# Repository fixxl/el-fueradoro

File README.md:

# el-fueradoro

This project contains a remotely controlled ignition system for audio-fireworks based on ATmega328P and RFM69CW.
Further information (in German) is given in [the user manual](https://cdn.jsdelivr.net/gh/fixxl/el-fueradoro@master/Manual/fueradoro.pdf).

What the system is capable of doing can be seen in our [new year's fireworks 2015](https://vimeo.com/116115628), [new year's fireworks 2016](https://vimeo.com/150594996), [new year's fireworks 2017](https://www.youtube.com/watch?v=Rc5oZRx3s50), [new year's fireworks 2018](https://www.youtube.com/watch?v=unH9tJSg1mw), and [new year's fireworks 2019](https://www.youtube.com/watch?v=GiKSdqZKpVQ).

Copyright:

All parts of the project are licensed under: https://creativecommons.org/licenses/by-nc/3.0/de/

Usage to perform commercial firework shows is explicitly granted.
Selling hard- and software derived from this project and usage within commercial systems is prohibited.

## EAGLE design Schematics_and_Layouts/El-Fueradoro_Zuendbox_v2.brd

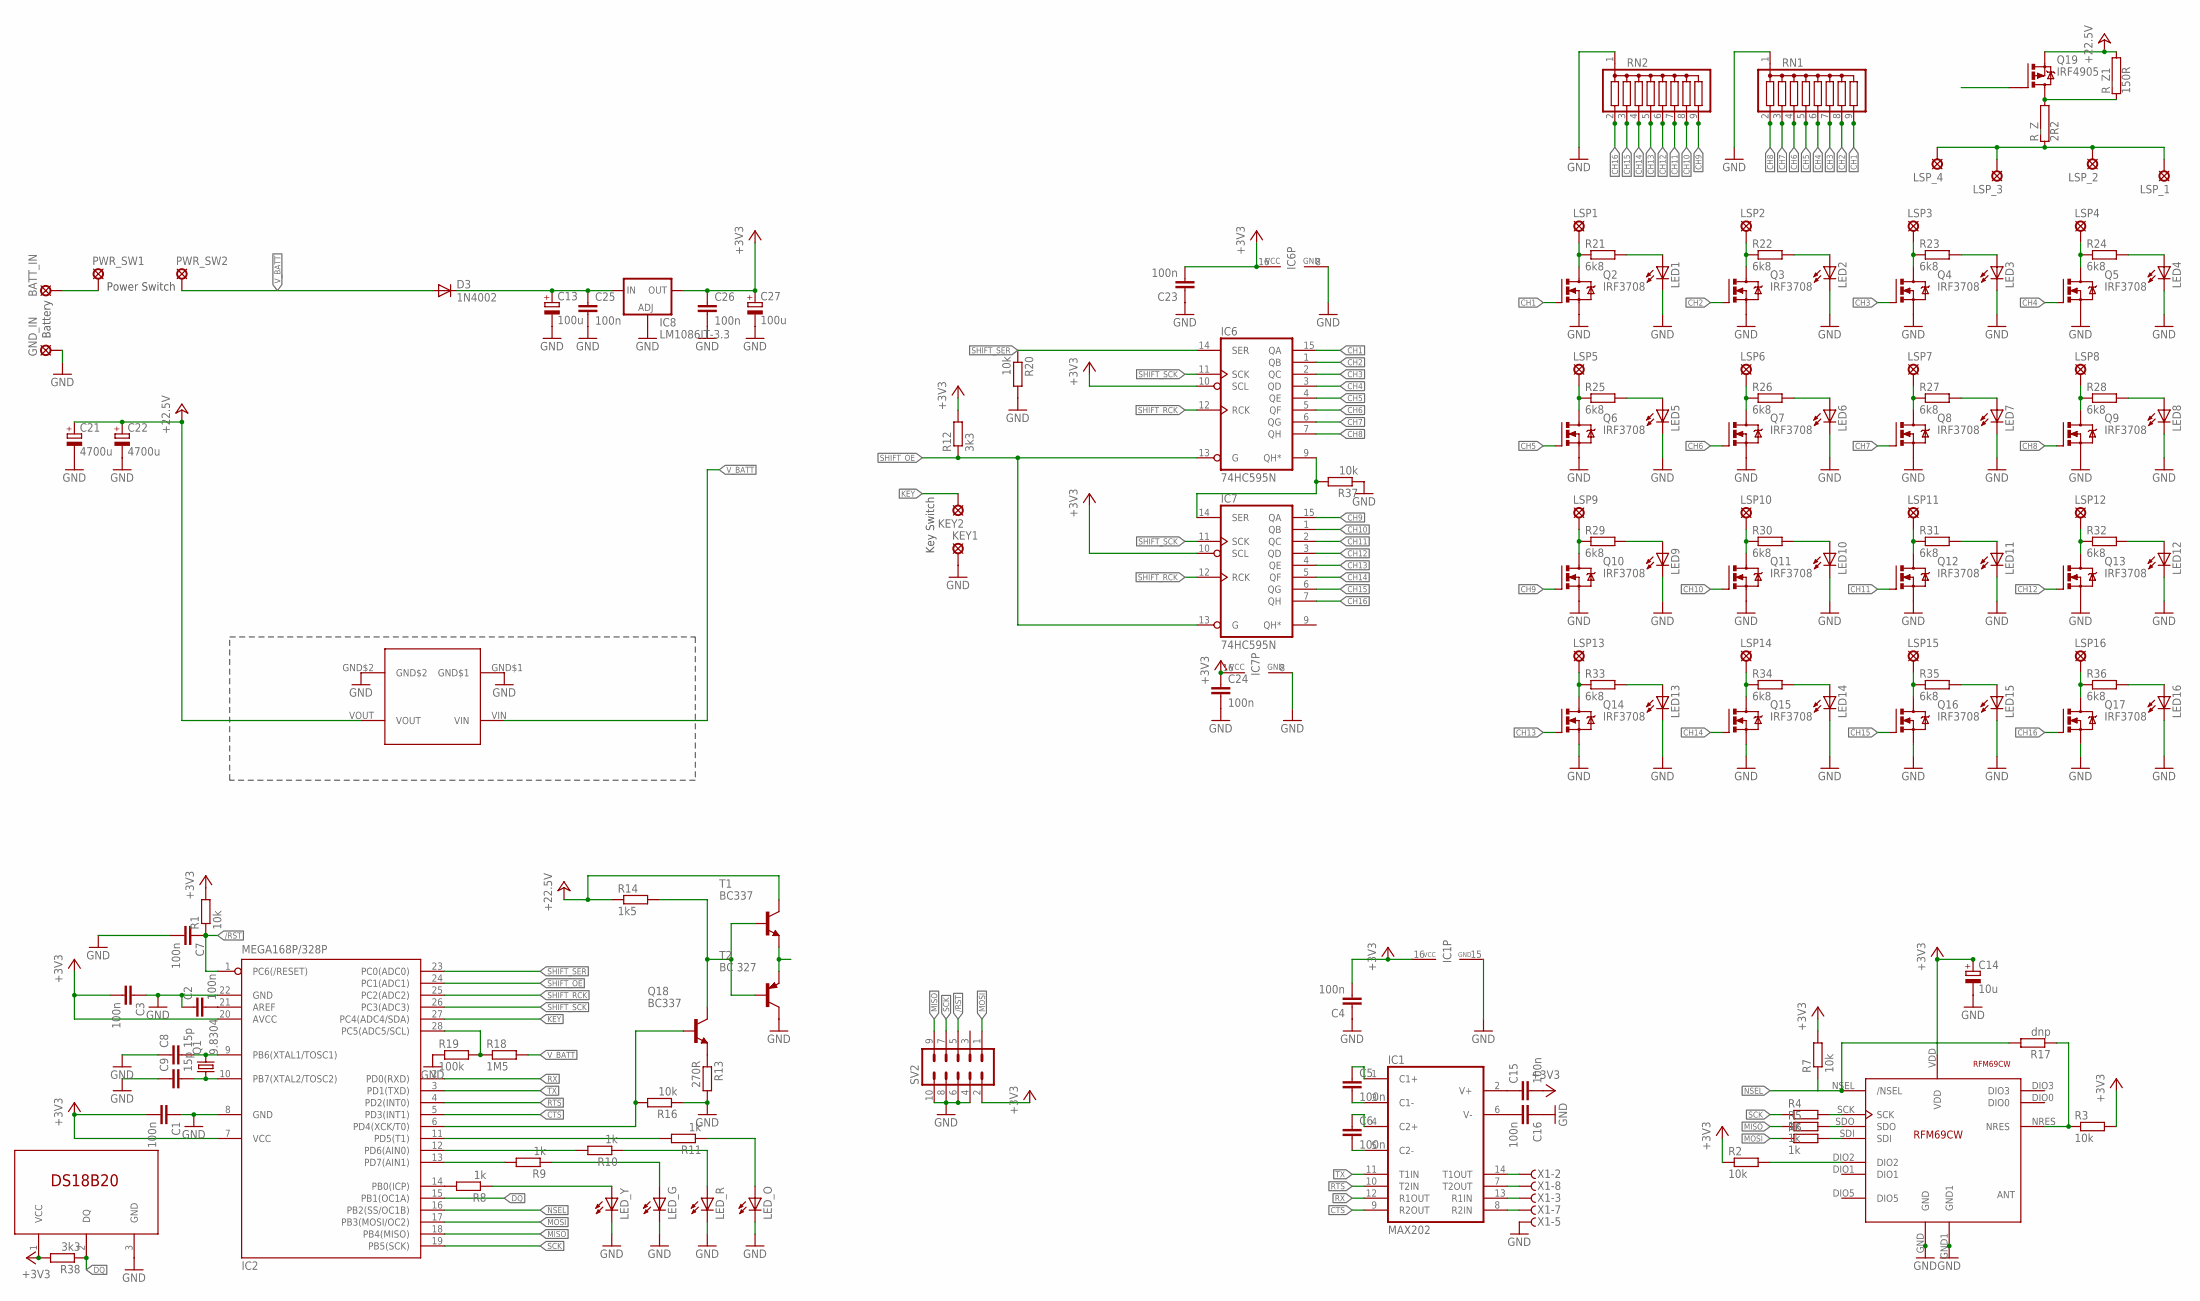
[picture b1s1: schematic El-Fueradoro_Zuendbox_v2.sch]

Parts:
BATT_IN: LSP10
C1, C2, C3, C4, C5, C6, C7, C15, C16, C23, C24, C25, C26: 100n; C025-024X044
C8, C9: 15p; C025-024X044
C13, C27: 100u; B45181A
C14: 10u; B45181A
C21, C22: 4700u; E7,5-18
D3: 1N4002; DO41-10
GND_IN: LSP10
IC1: MAX202; DIL16
IC2: MEGA168P/328P; DIL28-3
IC6, IC7: 74HC595N; DIL16
IC8: LM1086IT-3.3; TO220L1
KEY1, KEY2: LSP10
LED1, LED2, LED3, LED4, LED5, LED6, LED7, LED8, LED9, LED10, LED11, LED12, LED13, LED14, LED15, LED16: LED3MM
LED_G: LED5MM
LED_O: LED5MM
LED_R: LED5MM
LED_Y: LED5MM
LSP1: CH1; LSP11
LSP2: CH2; LSP11
LSP3: CH3; LSP11
LSP4: CH4; LSP11
LSP5: CH5; LSP11
LSP6: CH6; LSP11
LSP7: CH7; LSP11
LSP8: CH8; LSP11
LSP9: CH9; LSP11
LSP10: CH10; LSP11
LSP11: CH11; LSP11
LSP12: CH12; LSP11
LSP13: CH13; LSP11
LSP14: CH14; LSP11
LSP15: CH15; LSP11
LSP16: CH16; LSP11
LSP_1, LSP_2, LSP_3, LSP_4: LSP11
PWR_SW1, PWR_SW2: LSP10
Q1: 9.8304; HC49/S
Q2, Q3, Q4, Q5, Q6, Q7, Q8, Q9, Q10, Q11, Q12, Q13, Q14, Q15, Q16, Q17: IRF3708; TO220BV
Q18: BC337; TO92
Q19: IRF4905; TO220BV
R1, R2, R3, R7, R16, R20, R37: 10k; 0207/10
R4, R5, R6, R8, R9, R10, R11: 1k; 0207/10
R12, R38: 3k3; 0207/10
R13: 270R; 0207/10
R14: 1k5; 0207/10
R17: dnp; 0207/10
R18: 1M5; 0207/10
R19: 100k; 0207/10
R21, R22, R23, R24, R25, R26, R27, R28, R29, R30, R31, R32, R33, R34, R35, R36: 6k8; 0207/10
RN1, RN2: G08R; SIL9
R_Z: 2R2; KH214R-8
R_Z1: 150R; KH214R-8
SV2: ML10
T1: BC337; TO92
T2: BC 327; TO92
U$2: DS18B20; TO92-LINE
U$3: XL6009_MODULED; XL6009_PACK
U$4: RFM69CW
X1: F09HPS; F09HP

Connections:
+3V3: C1.2, C3.2, C4.2, C14.+, C15.2, C23.2, C24.1, C26.1, C27.+, IC1.16 (VCC), IC2.7 (VCC), IC2.20 (AVCC), IC6.10 (SCL), IC6.16 (VCC), IC7.10 (SCL), IC7.16 (VCC), IC8.2 (OUT), R1.2, R2.1, R3.2, R7.2, R12.2, R38.2, SV2.2, U$2.1 (VCC), U$4.VDD
+22_5V: C21.+, C22.+, Q19.S, R14.1, R_Z1.2, T1.3 (C), U$3.VOUT
/RST: C7.1, IC2.1 (PC6(/RESET)), R1.1, SV2.5
CH1: IC6.15 (QA), Q2.G, RN1.9
CH2: IC6.1 (QB), Q3.G, RN1.8
CH3: IC6.2 (QC), Q4.G, RN1.7
CH4: IC6.3 (QD), Q5.G, RN1.6
CH5: IC6.4 (QE), Q6.G, RN1.5
CH6: IC6.5 (QF), Q7.G, RN1.4
CH7: IC6.6 (QG), Q8.G, RN1.3
CH8: IC6.7 (QH), Q9.G, RN1.2
CH9: IC7.15 (QA), Q10.G, RN2.9
CH10: IC7.1 (QB), Q11.G, RN2.8
CH11: IC7.2 (QC), Q12.G, RN2.7
CH12: IC7.3 (QD), Q13.G, RN2.6
CH13: IC7.4 (QE), Q14.G, RN2.5
CH14: IC7.5 (QF), Q15.G, RN2.4
CH15: IC7.6 (QG), Q16.G, RN2.3
CH16: IC7.7 (QH), Q17.G, RN2.2
CTS: IC1.9 (R2OUT), IC2.5 (PD3(INT1))
DQ: IC2.15 (PB1(OC1A)), R38.1, U$2.2 (DQ)
DRVBASE: Q18.3 (C), R14.2, T1.2 (B), T2.2 (B)
GND: C1.1, C2.1, C3.1, C4.1, C7.2, C8.1, C9.1, C13.-, C14.-, C16.1, C21.-, C22.-, C23.1, C24.2, C25.2, C26.2, C27.-, GND_IN.MP, IC1.15 (GND), IC2.8 (GND), IC2.22 (GND), IC6.8 (GND), IC7.8 (GND), IC8.1 (ADJ), KEY1.MP, LED1.K (C), LED2.K (C), LED3.K (C), LED4.K (C), LED5.K (C), LED6.K (C), LED7.K (C), LED8.K (C), LED9.K (C), LED10.K (C), LED11.K (C), LED12.K (C), LED13.K (C), LED14.K (C), LED15.K (C), LED16.K (C), LED_G.K (C), LED_O.K (C), LED_R.K (C), LED_Y.K (C), Q2.S, Q3.S, Q4.S, Q5.S, Q6.S, Q7.S, Q8.S, Q9.S, Q10.S, Q11.S, Q12.S, Q13.S, Q14.S, Q15.S, Q16.S, Q17.S, R13.2, R16.1, R19.1, R20.2, R37.1, RN1.1, RN2.1, SV2.4, SV2.6, SV2.8, SV2.10, T2.3 (C), U$2.3 (GND), U$3.GND$1, U$3.GND$2, U$4.GND, U$4.GND1, X1.5 (F)
KEY: IC2.27 (PC4(ADC4/SDA)), KEY2.MP
MISO: IC2.18 (PB4(MISO)), R5.1, SV2.9
MOSI: IC2.17 (PB3(MOSI/OC2)), R6.1, SV2.1
unnamed: BATT_IN.MP, PWR_SW1.MP
unnamed: C13.+, C25.1, D3.C, IC8.3 (IN)
unnamed: IC2.6 (PD4(XCK/T0)), Q18.2 (B), R16.2
unnamed: Q18.1 (E), R13.1
unnamed: LSP_1.MP, LSP_2.MP, LSP_3.MP, LSP_4.MP, R_Z.1
unnamed: Q19.D, R_Z.2, R_Z1.1
unnamed: R2.2, U$4.DIO2
unnamed: R4.2, U$4.SCK
unnamed: R5.2, U$4.SDO
unnamed: R6.2, U$4.SDI
unnamed: R3.1, R17.1, U$4.NRES
unnamed: C2.2, IC2.21 (AREF)
unnamed: C9.2, IC2.10 (PB7(XTAL2/TOSC2)), Q1.1
unnamed: C5.1, IC1.1 (C1+)
unnamed: C5.2, IC1.3 (C1-)
unnamed: C6.1, IC1.4 (C2+)
unnamed: C6.2, IC1.5 (C2-)
unnamed: C8.2, IC2.9 (PB6(XTAL1/TOSC1)), Q1.2
unnamed: IC2.13 (PD7(AIN1)), R9.2
unnamed: IC2.12 (PD6(AIN0)), R10.2
unnamed: IC2.11 (PD5(T1)), R11.2
unnamed: LED_O.A, R11.1
unnamed: IC2.14 (PB0(ICP)), R8.2
unnamed: LED_R.A, R10.1
unnamed: LED_G.A, R9.1
unnamed: LED_Y.A, R8.1
unnamed: IC2.28 (PC5(ADC5/SCL)), R18.1, R19.2
unnamed: C15.1, IC1.2 (V+)
unnamed: C16.2, IC1.6 (V-)
unnamed: IC6.9 (QH*), IC7.14 (SER), R37.2
unnamed: LSP1.MP, Q2.D, R21.1
unnamed: LSP2.MP, Q3.D, R22.1
unnamed: LSP3.MP, Q4.D, R23.1
unnamed: LSP4.MP, Q5.D, R24.1
unnamed: LSP5.MP, Q6.D, R25.1
unnamed: LSP6.MP, Q7.D, R26.1
unnamed: LSP7.MP, Q8.D, R27.1
unnamed: LSP8.MP, Q9.D, R28.1
unnamed: LSP9.MP, Q10.D, R29.1
unnamed: LSP10.MP, Q11.D, R30.1
unnamed: LSP11.MP, Q12.D, R31.1
unnamed: LSP12.MP, Q13.D, R32.1
unnamed: LSP13.MP, Q14.D, R33.1
unnamed: LSP14.MP, Q15.D, R34.1
unnamed: LSP15.MP, Q16.D, R35.1
unnamed: LSP16.MP, Q17.D, R36.1
unnamed: LED1.A, R21.2
unnamed: LED2.A, R22.2
unnamed: LED3.A, R23.2
unnamed: LED4.A, R24.2
unnamed: LED5.A, R25.2
unnamed: LED6.A, R26.2
unnamed: LED7.A, R27.2
unnamed: LED8.A, R28.2
unnamed: LED9.A, R29.2
unnamed: LED10.A, R30.2
unnamed: LED11.A, R31.2
unnamed: LED12.A, R32.2
unnamed: LED13.A, R33.2
unnamed: LED14.A, R34.2
unnamed: LED15.A, R35.2
unnamed: LED16.A, R36.2
NSEL: IC2.16 (PB2(SS/OC1B)), R7.1, R17.2, U$4.NSEL (/NSEL)
PC_CTS_IN: IC1.7 (T2OUT), X1.8 (F)
PC_RTS_OUT: IC1.8 (R2IN), X1.7 (F)
PC_RX_IN: IC1.14 (T1OUT), X1.2 (F)
PC_TX_OUT: IC1.13 (R1IN), X1.3 (F)
PMOSG: Q19.G, T1.1 (E), T2.1 (E)
RTS: IC1.10 (T2IN), IC2.4 (PD2(INT0))
RX: IC1.12 (R1OUT), IC2.2 (PD0(RXD))
SCK: IC2.19 (PB5(SCK)), R4.1, SV2.7
SHIFT_OE: IC2.24 (PC1(ADC1)), IC6.13 (G), IC7.13 (G), R12.1
SHIFT_RCK: IC2.25 (PC2(ADC2)), IC6.12 (RCK), IC7.12 (RCK)
SHIFT_SCK: IC2.26 (PC3(ADC3)), IC6.11 (SCK), IC7.11 (SCK)
SHIFT_SER: IC2.23 (PC0(ADC0)), IC6.14 (SER), R20.1
TX: IC1.11 (T1IN), IC2.3 (PD1(TXD))
V_BATT: D3.A, PWR_SW2.MP, R18.2, U$3.VIN

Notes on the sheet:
Power Switch
Battery
Key Switch

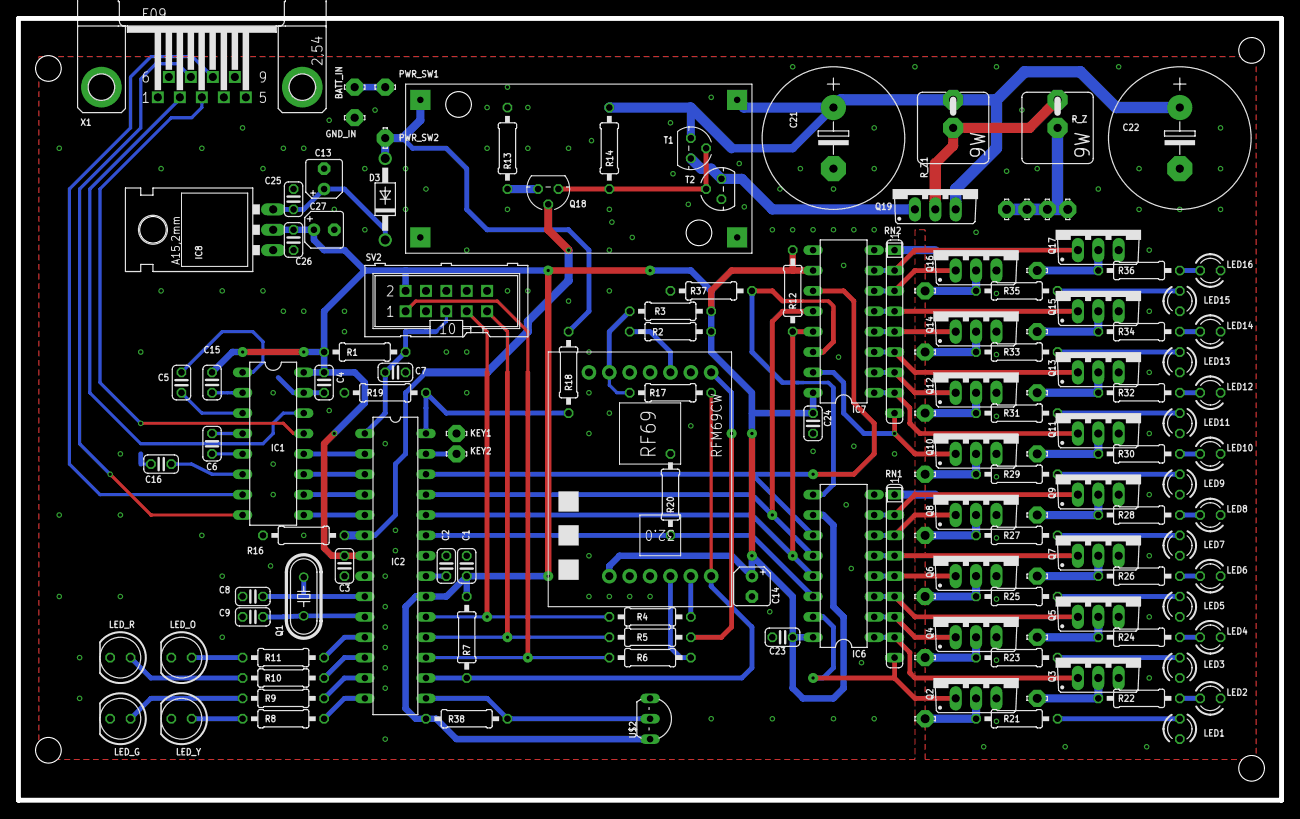
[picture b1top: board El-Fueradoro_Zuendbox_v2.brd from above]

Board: 2 copper layers, 157.5 x 97.5 mm, 139 parts (0 on the bottom side), 103 nets.

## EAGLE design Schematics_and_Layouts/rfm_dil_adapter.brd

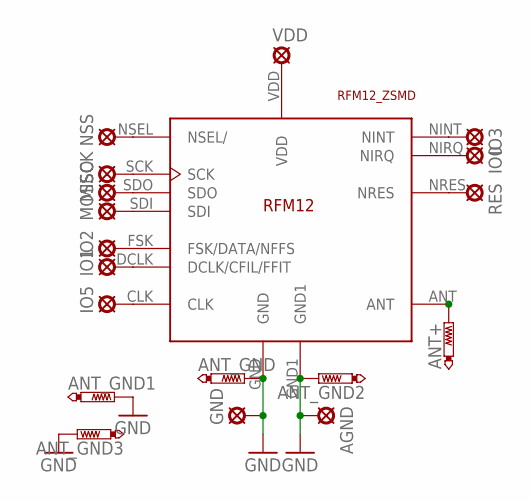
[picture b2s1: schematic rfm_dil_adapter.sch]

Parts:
AGND: LSP10
ANT+: PTR1TP20SQ; TP20SQ
ANT_GND, ANT_GND1, ANT_GND2, ANT_GND3: PTR1TP20SQ; TP20SQ
GND: LSP10
IO0, IO1, IO2, IO3, IO5: LSP10
MISO: LSP10
MOSI: LSP10
NSS: LSP10
RES: LSP10
SCK: LSP10
U$1: RFM12_ZSMD; RFM12_Z
VDD: LSP10

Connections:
ANT: ANT+.TP, U$1.ANT
GND: AGND.MP, ANT_GND.TP, ANT_GND1.TP, ANT_GND2.TP, ANT_GND3.TP, GND.MP, U$1.GND, U$1.GND1
unnamed: IO5.MP, U$1.CLK
unnamed: IO1.MP, U$1.DCLK (DCLK/CFIL/FFIT)
unnamed: IO2.MP, U$1.FSK (FSK/DATA/NFFS)
unnamed: MOSI.MP, U$1.SDI
unnamed: MISO.MP, U$1.SDO
unnamed: SCK.MP, U$1.SCK
unnamed: NSS.MP, U$1.NSEL (NSEL/)
unnamed: RES.MP, U$1.NRES
unnamed: IO0.MP, U$1.NIRQ
unnamed: IO3.MP, U$1.NINT
VDD: U$1.VDD, VDD.MP

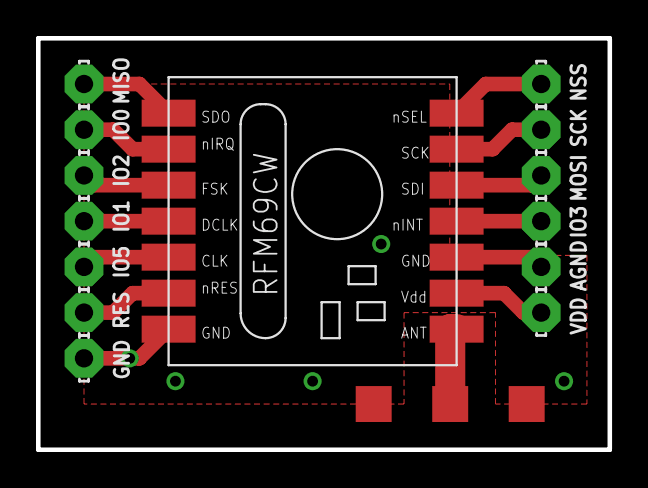
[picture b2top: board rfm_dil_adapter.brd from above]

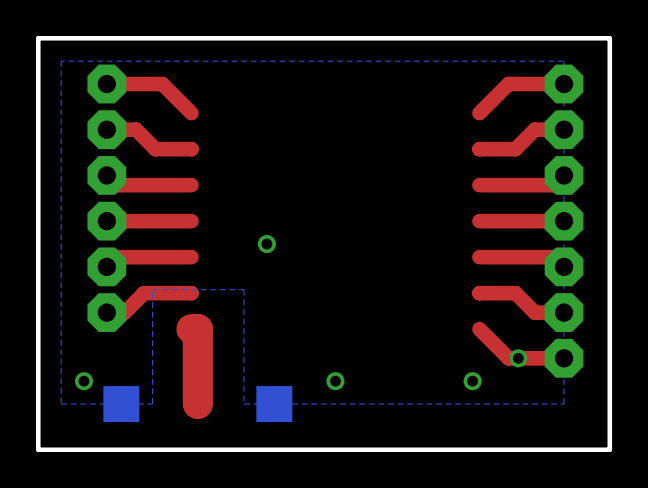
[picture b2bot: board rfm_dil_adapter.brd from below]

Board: 2 copper layers, 31.8 x 22.9 mm, 19 parts (2 on the bottom side), 13 nets.

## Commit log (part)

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2014-12-29 Fixed Hardware-SPI-problem which was due to double usage of identical variables for RFM12 and RFM69.
2014-12-31 Recommit after bad changes (Rev. 85)
2014-12-31 Replaced HARDWARE_SPI by HARDWARE_SPI_69 and HARDWARE_SPI_12 respectively during initialization. Reduced SPI-frequency.
2015-01-01 Only allowing remote reconfiguration of device numbers when device is not armed
2015-01-01 Corrected wrong ID-order and unified ID-order in other cases to unique before slave
2015-01-01 LCD lines are now written completely, no leftovers from former commands
2015-01-02 Bugfixes and manual update
2015-01-03 Error correction
2015-01-06 Omitting AFC Fixing issue of slow restart when not connected to terminal program Setting uart-timeout to realistic value Added confirmation-dialogue to remote ID-update Further bugfixes and cosmetic 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
2015-01-07 Rx-Tweak for RFM69 to avoid deadlocks
2015-01-08 Found and implemented a way to find out if connected device is a transmitter or a ignition box. Now it should be impossible to configure a ignition box as transmitter.
2015-01-09 Added security features and device-type-display in configuration routine.
2015-01-09 Further updates and cleanups
2015-01-09 AFC back in charge
2015-01-10 Added repeats to every transmission, not only ignition orders
2015-01-11 Buxfixes on multiple transmitting.
2015-01-12 V 111
2015-01-13 RFM can now be read out via UART (especially interesting for RFM69)
2015-01-15 Big manual update! Some adjustments in update-software to avoid crashes. Reducing of screen-output messages to save memory.
2015-01-16 Code documentation should now be completely in English. Moved address-save-function to other module.
2015-01-16 New repository structure
2015-01-16 Added EAGLE files!
2015-01-18 Added bill of materials
2015-01-20 Added size-information-output for Hexfiles/build_hexfiles.bat Extended manual and added BOMs BOM-Update (final one, hopefully!)
2015-01-20 The manual is still growing
2015-01-21 Layout fixes Additions to manual once again
2015-01-22 Manual update
2015-01-28 Some GUI-preperations!
2015-01-29 Code size optimization Initial blinking now shows slave-id
2015-01-29 Ladies and Gentlemen, we have a GUI! To check it out, the newest firmware has to be flashed on every device first!
2015-01-30 Strict transmitter-ignition device separation
2015-01-31 Secure start-up-sequence Better GUI Removed useless empty line on config
2015-02-01 Removed redundant code
2015-02-08 RFM-access added to GUI
2015-02-21 Drill distance adjusted, layouts up to date
2015-03-10 Only some additional whitespaces
2015-03-13 Formatting...
2015-03-16 Manual-sources added
2015-03-22 Manual...
2015-03-25 Manual formatting
2015-03-30 RFM69-tests
2015-03-31 Updated Manual Still trying to get better config for RFM69
2015-03-31 Updated repository-URL in manual
2015-04-06 Some more pictures in the manual + additional information New RSSI-timeout-interval for RFM69 Terminal display improvement
2015-04-07 Removed unnecessary on-off-commands Rx-Restart on timeouts now part of function rfm_receiving() Rx-Restart on timeouts removed from pyro.c
2015-04-08 Added missing chip-selection Improved bandwidth-related settings
2015-04-08 Updated hexfiles
2015-04-09 Shrink repository
2015-04-12 Deleted files not necessary for compilation of the manual
2015-04-12 Optimized RSSI-threshold for RFM69 Corrected cable lengths in the manual
2015-05-02 New added GUI-content to manual
2015-05-05 RSSI-value added to LCD
2015-05-07 Manual corrections and improvements
2015-05-10 Manual improvements
2015-05-13 Manual
2015-05-20 Took care of unused pin
2015-05-21 Manual improved, clarified ISP connection
2015-06-09 Added compatibility comment to rfm69.c Manual updated and a bit more error corrected
2015-07-03 Manual modifications
2015-07-11 Some improvements in the manual
2015-07-18 Updated the manual once again
2015-07-24 Manual update (RFM-access)
2015-07-26 Added link to firework
2015-08-13 New Eclipse-Version (Mars)
2015-08-13 Added function descriptions to 1wire-lib
2015-08-14 New pictures to show PyroIgnitionControl-configuration
2015-08-14 Funny test
2015-08-15 Case-modding-section extended
2015-08-16 Incorporating recent changes
2015-08-18 Manual size shrunk, pictures resized/resampled
2015-08-25 New GCC-compiler version
2015-09-06 Optical improvement on manual transmission
2015-09-20 Some debugging in the manual
2015-11-09 1-wire-timing corrected
2015-11-11 Better temperature calculation routine
2015-11-13 Unitary source-code formatting No functional changes
2015-11-16 Formatted source code Manual update (Credits)
2015-11-18 Sourcecode beautification Added disabling of shift-registers before reset Manual updated Updated hexfiles
2015-11-22 1-wire-fix in unused function, not really relevant for system Code-translation and beautification
2015-12-01 Option to use hardware-spi with shift register added
2015-12-01 Added missing newline in manual sending routine
2015-12-01 Higher output power for RFM59
2015-12-02 Reset transmission power to 8 dBm Hexfiles updated Manual layout improved
2015-12-02 Code formatting
2015-12-03 Created a high-power-version of the Atmega328p-RFM69-firmware, where 13 dBm is the standard output power of the radio module.
    Manual updated and reformatted
2015-12-04 Extended info on RSSI
2015-12-13 Added datasheet-links to manual Table-unification
2015-12-14 Linebreaks and thesaurus
2015-12-21 Removed the "channel already fired?"-checks
2015-12-21 Manual changes
2015-12-27 Changed Slave-ID-blinking from green/orange to yellow/orange
2015-12-29 Update pyro.c
    Wrong blinking sequence fixed
2015-12-29 Hexfiles updated
2016-02-24 Corrected spelling error
2016-03-06 Added windows-GUI-update tool
2016-03-17 Changed while-condition order to guarantee for proper timeouts (C shortcut-evaluation)
2016-03-17 Added windows-update-gui to manual Some more "shortcut evaluation"-driven changes
2016-03-21 More sophisticated method of calculating Tx-Timeout
2016-03-21 New tool for controlling ignition schemes (no manual update yet)
2016-04-23 Added Gerber Files
2016-04-26 Added hints for double ignition
2016-05-03 GCC version now displaying before build Built hexfiles with GCC 6.1
2016-05-04 Improved build_hexfiles.bat
2016-05-04 Improved build-switches, smaller hexfiles!
2016-05-06 No substantial change, just --relax to -mrelax
2016-05-06 Compiler options changed for Eclipse-project
2016-05-10 Initial transmitter sequence now compliant with loopcount mechanism
2016-05-29 Added LCD-timeout
2016-08-20 Type errors
2016-09-07 New styling for the manual
2016-09-07 Small bugfixing from last update
2016-09-08 Valid eBay-links
2016-09-14 Manual updated
2016-09-16 Unit spacing and footnotes with updated PDF
2016-09-30 Optimized timeout in RFM69 Manual update on radio-range
2016-11-24 Correct transmission of transmitter's armed-status
2016-12-01 Handling of pin in case of missing temperature sensor
2016-12-10 Preparations for next generation, old boxes will still be fully supported
2016-12-18 Transmitter-arming implemented in GUI
2017-05-25 Larger update: Frequency deviation adaption Bills of Material No more RFM12-support
2017-05-28 Implemented AES-encryption
2017-07-13 Hexfiles compiled with new AVR-GCC 7.1 Manual corrections
2017-07-14 Only newest manual version available
2017-07-14 One more try
2017-07-22 Bugfix in Zündbox_v2-Gerber-Files Kompiliert mit AVR-GCC 8
2017-08-05 Manual update Display of internal AES-Key for comparison
2017-10-01 BOM correction
2017-10-25 BOM fixes
2017-12-15 Korrektur sprachlicher Fehler im Handbuch
2018-01-05 Angleichung von Handbuch und Layouts
2018-01-22 Dynamisierter Rx-Timeout
2018-05-14 Workaround for string comparison
2018-08-04 Cumulative update of some changes
2018-08-15 Changes in v3-firmware
2018-08-15 Impedance listing
2018-08-20 v3-bugfix for impedance calculator
2018-08-21 Project settings for v3
2018-08-22 Automatic dummy conversion for every ADC-measurement
2018-09-08 Working and tested v3 with channel LEDs and impedance measurement
2018-09-08 Added some v3-documentation
2018-09-20 Implemented impedance re-reading upon disarming
2018-10-15 v3 impedance update now triggerable by turning key switch
2018-11-03 Consistency
2019-01-11 Setting v3 as standard for flash
2019-01-24 RFM-Adapter-Gerber Files
2019-01-26 Finally added some raspEasyFire-stuff to the manual
2019-01-27 Additional subsection
2019-03-16 AVRDUDE update
2019-03-16 Intelligent Bootloader-Flasher avoiding verification error for EFUSE
2019-05-21 Time triggered channel measurements
2019-05-25 Reorganized ignitions and interrupts
2019-05-30 Impedance read condition refined
2019-05-31 Minor fixes on transmission delays
2019-06-10 Added datecode and timecode to firmware files for easier version recognition
2019-06-29 Timestamps and manual
2019-09-16 New compiler for hexfiles Some additions to the manual
2019-09-17 Some more information on bootloader-flashing in the manual
2019-09-25 Preparations for easier future expandability to more than 30 boxes
2019-09-29 Timestring-Fix and LED signaling bugfix
2019-09-29 Timestamp fix and LED fix for v3
2019-10-04 Found final startup LED solution
2019-10-04 Flexible ID limit, can be provisioned at compiletime
2019-10-06 New buildscript taking MAX_ID as parameter and checking for plausibility
2019-10-11 Fixed another MAX_ID/MAX_COM_ARRAYSIZE confusion Hexfiles compiled with MAX_ID=50
2019-10-22 Extendability improvements
2019-11-24 Update README because of RawGit shutdown
    RawGit will be shut down in the near future (we are already past its "served at least until" time), so a change to the jsDelivr service is a good idea).
2019-11-27 Impedance transmission ready for 32 channels
2019-12-08 Replaced hardcoded channel maximum number with define
2019-12-10 Encorporated some cppcheck hints
2019-12-15 Spaces
2019-12-16 Make the channel number a part of the box parameters
2019-12-26 Adjustable ignition time
2020-01-02 Gerber
2020-03-16 Disable v3 channel LEDs when arming slave
2020-03-16 Bugfix concerning impedance measurement on armed slaves
2020-03-28 KiCad schematic files for Raspberry Pi pcb
2020-03-30 Extended duration of channel LED test phase
2020-03-31 Typo
2020-05-12 Changed RF parameters (smaller deviation, smaller rx bandwidth)
2020-05-18 New image naming scheme, omitting 8 dBm versions
2020-05-30 Gerber files for RFM69HCW adapter
2020-05-30 Bugfix and code cleanup for proper function of RFM69HCW
2020-06-08 Corrected wrong GPIO for RFM-CS in v1/v2
2020-06-09 Added RFM init fail indicator (orange and green LED permanently on)
2020-06-15 User manual
2020-11-22 RSSI-Threshold remotely programmable
2020-11-23 Delivering RSSI value as part of parameter protocol Fixed typo in manual
2021-01-17 Timeout adjustment
2021-01-17 Packet delay config
2021-01-19 Check for incoming packets during impedance measurement and stop measuring if required
2021-02-06 Debouncing and Minimodul-Firmware
2021-03-28 Eclipse update
2021-04-02 Multicue capabilities
2021-04-30 Mini module operating frequency, new bootloader and test routine
2021-05-02 Battery voltage calculation for Mini module
2021-07-30 MiniModul-Bugfix: Channel LEDs now turning off after being triggered remotely
2021-08-01 New El Fueradoro Logo
2021-08-18 Igniter choice bugfix
2021-08-21 Reset channel timeout counter every time a channel is triggered - making retriggering possible while channel already active
2021-09-06 Implementation of squelch value auto-adjustment
2021-09-07 Amendments for Minimodul
2021-09-07 Hexfile update
2021-09-08 Control loop smoothing
2021-09-14 Changed output for terminal command hw to enable device identification (number of channels and RFM type)
2022-01-12 Optimized wait time after packet reception
2022-02-24 Add some to ignition time window
2022-03-10 Introducing delay between repetitions to give Rx a better chance to sync
2022-03-27 Frequency change possibility
2022-03-29 Frequency setting option
2022-03-31 Fixed inconsistent init of RFM register
2022-04-01 Avoid timeout if other boxes send impedance lists
2022-04-01 Handling timeout case for impedance measurement setting
2022-05-22 Auto squelch finetune: don't open up more in armed state if certain level is already reached
2022-06-29 Force number of DM13A channels to a multiple of 16
